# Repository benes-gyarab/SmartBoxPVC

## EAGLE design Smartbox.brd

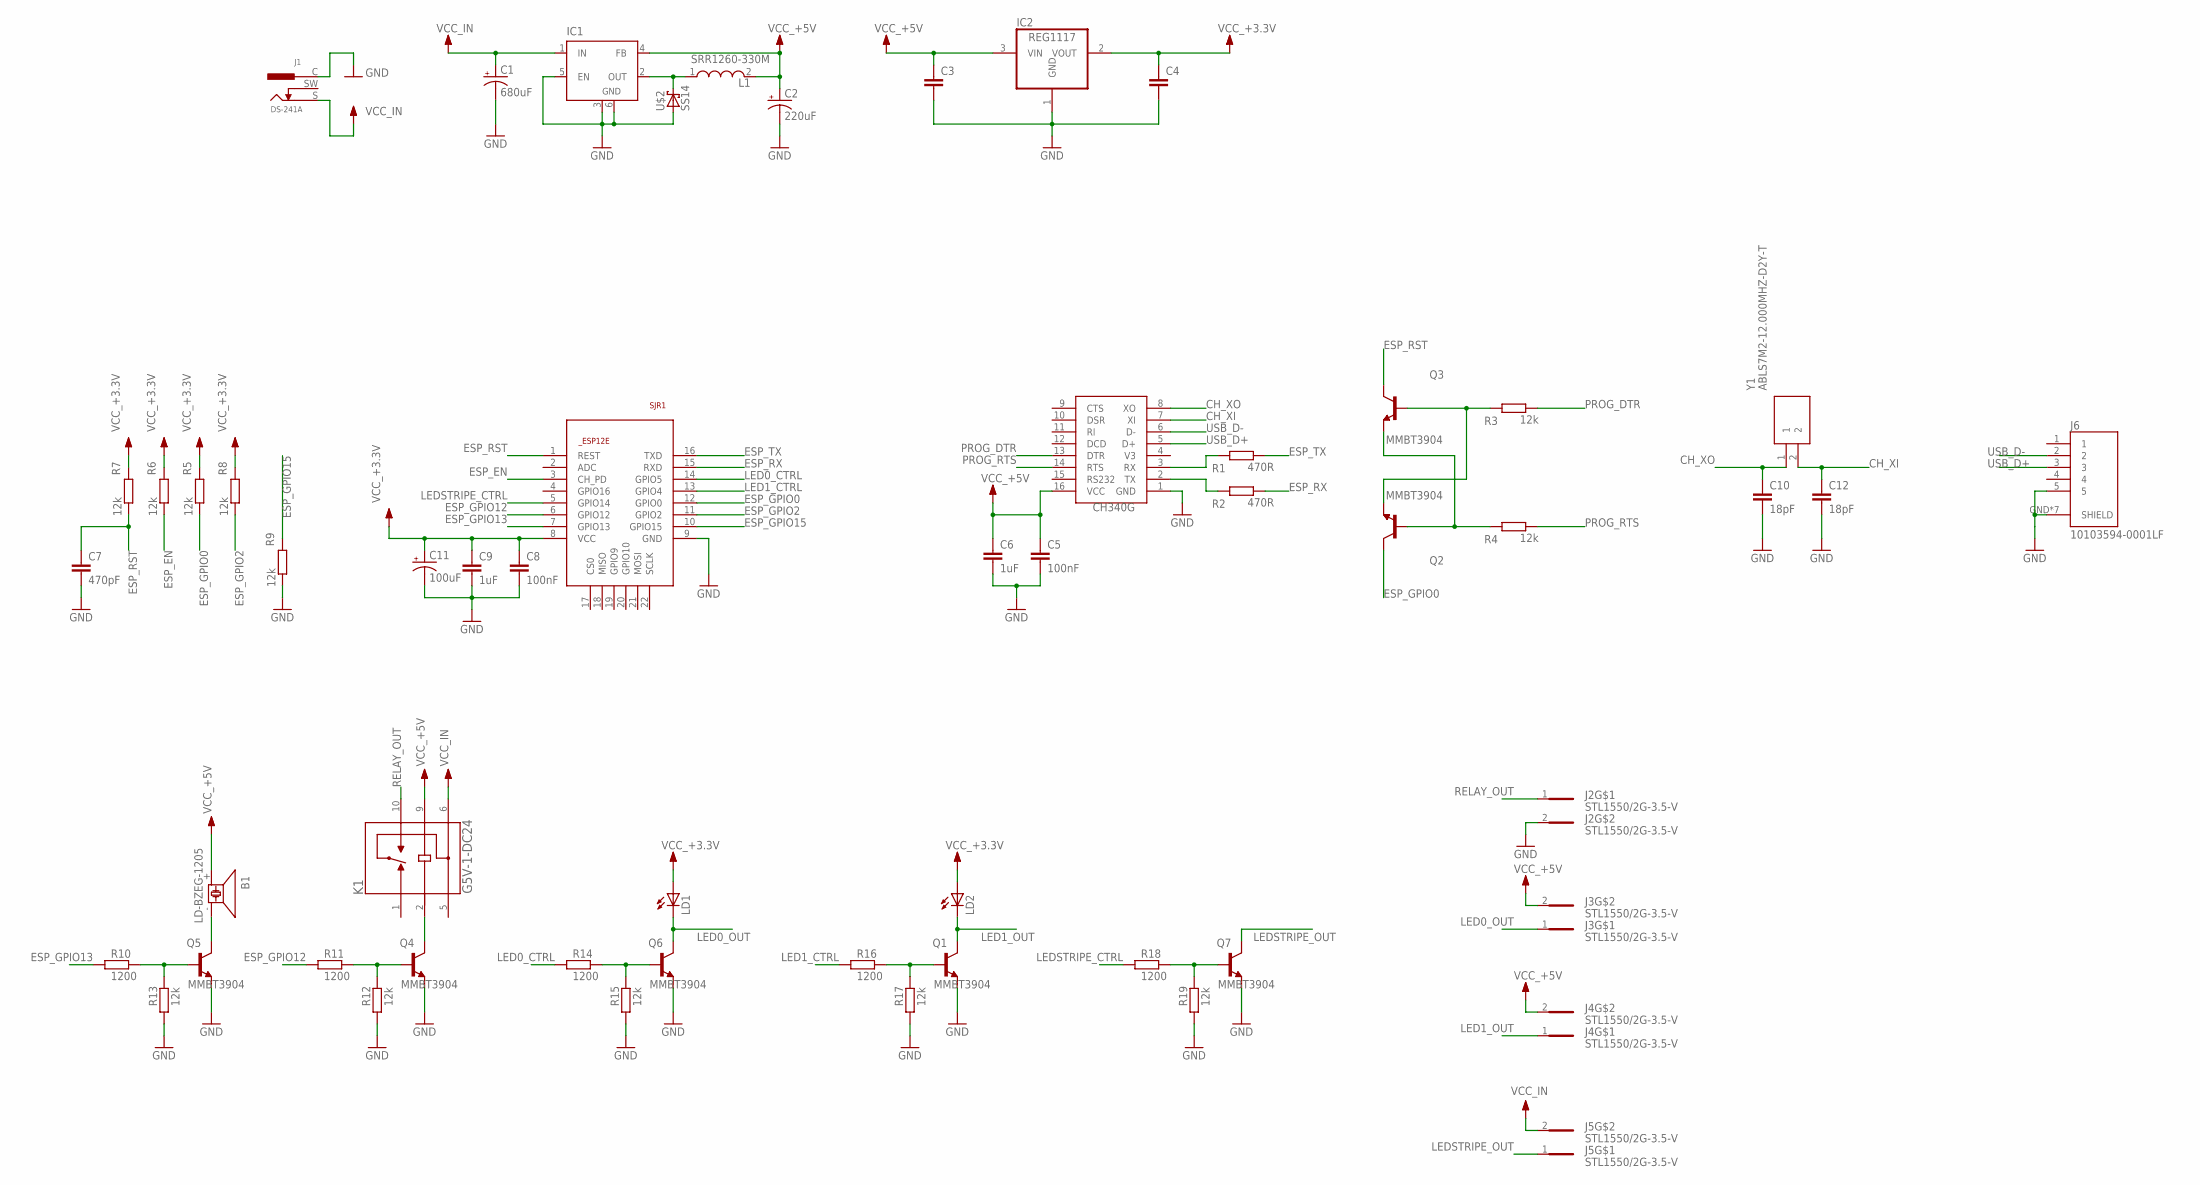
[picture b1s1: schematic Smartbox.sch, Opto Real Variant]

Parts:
B1: LD-BZEG-1205; LD-BZEG-12XX
C1: 680uF; PANASONIC_D
C2: 220uF; PANASONIC_D
C3, C4: C-EUC0805; C0805
C5, C8: 100nF; C0805
C6, C9: 1uF; C0805
C7: 470pF; C0805
C10, C12: 18pF; C0805
C11: 100uF; PANASONIC_D
IC1: LM2596S; TO263-5
IC2: REG1117; SOT223
J1: DS-241A; DS-241
J2, J3, J4, J5: STL1550/2G-3.5-V; STL1550/2G-3.5-V-GREEN
J6: 10103594-0001LF
K1: G5V-1-DC24
L1: SRR1260-330M; SRR1260-150M
LD1, LD2: LEDCHIPLED_0805; CHIPLED_0805
Q1, Q2, Q3, Q4, Q5, Q6, Q7: MMBT3904; SOT23
R1, R2: 470R; R0805
R3, R4, R5, R6, R7, R8, R9, R12, R13, R15, R17, R19: 12k; R0805
R10, R11, R14, R16, R18: 1200; R0805
SJR1: ESP8266-12EESP12E; ESP8266-ESP12E
U$2: SS14; DO-214AC
U$3: CH340G; SOIC16
Y1: ABLS7M2-12.000MHZ-D2Y-T; ABLS7M216000MHZD2YT

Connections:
CH_XI: C12.1, U$3.7 (XI), Y1.2
CH_XO: C10.1, U$3.8 (XO), Y1.1
ESP_EN: R6.2, SJR1.3 (CH_PD)
ESP_GPIO0: Q2.3 (C), R5.2, SJR1.12 (GPIO0)
ESP_GPIO2: R8.2, SJR1.11 (GPIO2)
ESP_GPIO12: R11.1, SJR1.6 (GPIO12)
ESP_GPIO13: R10.1, SJR1.7 (GPIO13)
ESP_GPIO15: R9.1, SJR1.10 (GPIO15)
ESP_RST: C7.1, Q3.3 (C), R7.2, SJR1.1 (REST)
ESP_RX: R2.2, SJR1.15 (RXD)
ESP_TX: R1.2, SJR1.16 (TXD)
GND: C1.-, C2.-, C3.2, C4.2, C5.2, C6.2, C7.2, C8.2, C9.2, C10.2, C11.-, C12.2, IC1.3 (GND), IC1.5 (EN), IC1.6 (GND), IC2.1 (GND), J1.C, J2.2, J6.5, J6.GND (SHIELD), J6.GND$1 (SHIELD), J6.GND$2 (SHIELD), J6.S1 (SHIELD), J6.S2 (SHIELD), J6.S3 (SHIELD), J6.S4 (SHIELD), Q1.2 (E), Q4.2 (E), Q5.2 (E), Q6.2 (E), Q7.2 (E), R9.2, R12.1, R13.1, R15.1, R17.1, R19.1, SJR1.9 (GND), U$2.A, U$3.1 (GND)
LED0_CTRL: R14.1, SJR1.14 (GPIO5)
LED0_OUT: J3.1, LD1.C, Q6.3 (C)
LED1_CTRL: R16.1, SJR1.13 (GPIO4)
LED1_OUT: J4.1, LD2.C, Q1.3 (C)
LEDSTRIPE_CTRL: R18.1, SJR1.5 (GPIO14)
LEDSTRIPE_OUT: J5.1, Q7.3 (C)
unnamed: R1.1, U$3.3 (RX)
unnamed: R2.1, U$3.2 (TX)
unnamed: Q2.2 (E), Q3.1 (B), R3.1
unnamed: Q2.1 (B), Q3.2 (E), R4.1
unnamed: K1.2, Q4.3 (C)
unnamed: Q5.1 (B), R10.2, R13.2
unnamed: B1.-, Q5.3 (C)
unnamed: Q1.1 (B), R16.2, R17.2
unnamed: Q4.1 (B), R11.2, R12.2
unnamed: Q6.1 (B), R14.2, R15.2
unnamed: Q7.1 (B), R18.2, R19.2
unnamed: IC1.2 (OUT), L1.1, U$2.C
PROG_DTR: R3.2, U$3.13 (DTR)
PROG_RTS: R4.2, U$3.14 (RTS)
RELAY_OUT: J2.1, K1.10
USB_D+: J6.3, U$3.5 (D+)
USB_D-: J6.2, U$3.6 (D-)
VCC_+3.3V: C4.1, C8.1, C9.1, C11.+, IC2.2 (VOUT), LD1.A, LD2.A, R5.1, R6.1, R7.1, R8.1, SJR1.8 (VCC)
VCC_+5V: B1.+, C2.+, C3.1, C5.1, C6.1, IC1.4 (FB), IC2.3 (VIN), J3.2, J4.2, K1.9, L1.2, U$3.16 (VCC)
VCC_IN: C1.+, IC1.1 (IN), J1.S, J5.2, K1.6

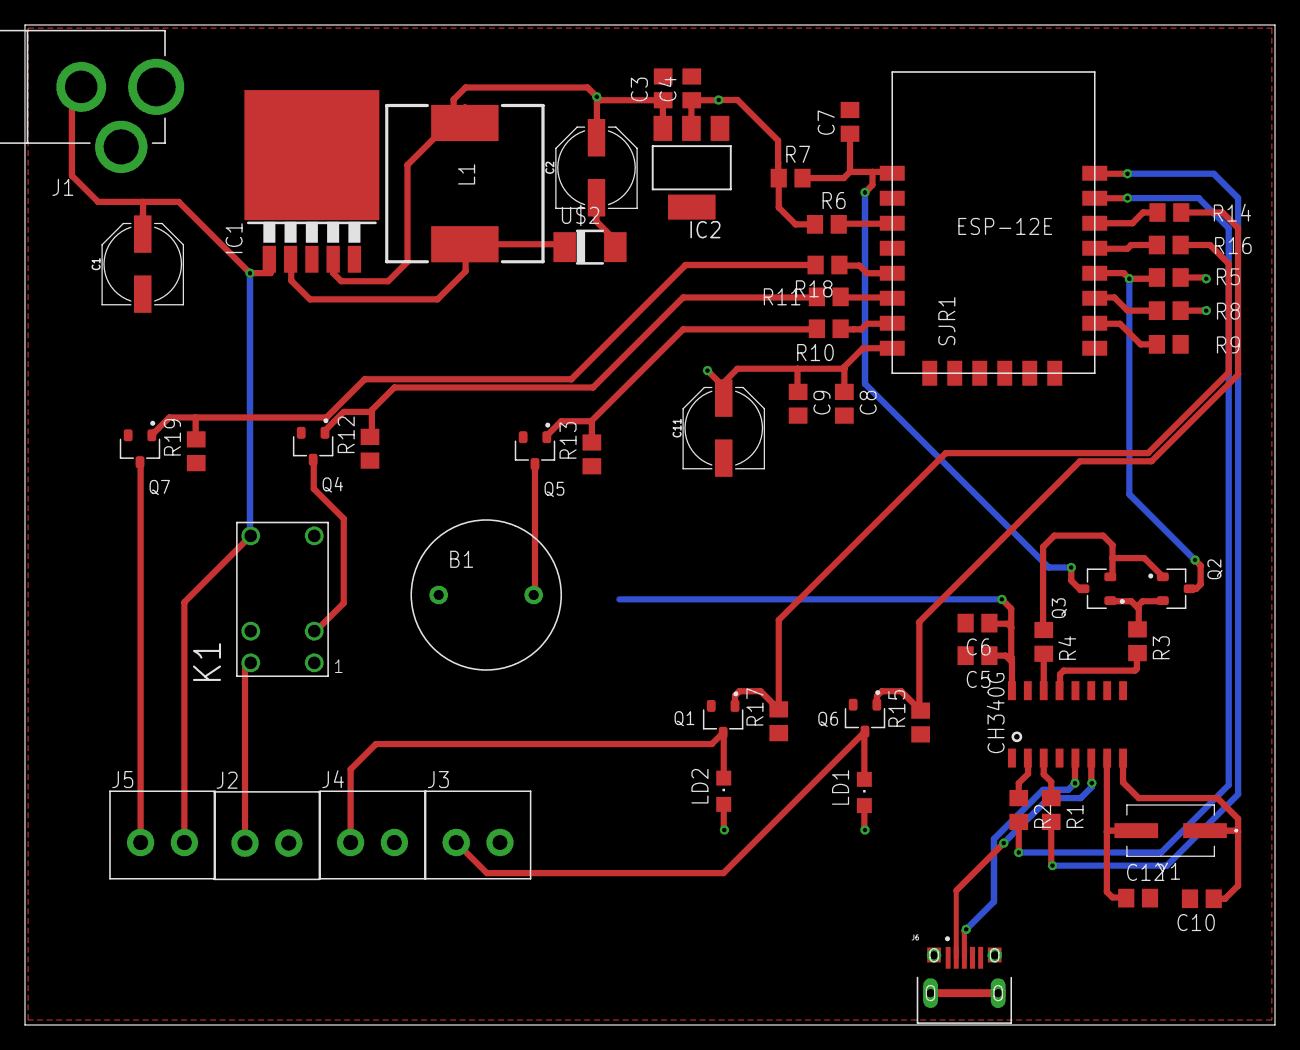
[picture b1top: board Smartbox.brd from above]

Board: 2 copper layers, 100.0 x 80.0 mm, 55 parts (0 on the bottom side), 38 nets.

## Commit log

2020-03-17 SmartBoxFixes
2020-04-29 Uprava

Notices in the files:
parts and their libraries:
SparkFun-Capacitors: Licensing: Creative Commons ShareAlike 4.0 International - https://creativecommons.org/licenses/by-sa/4.0
